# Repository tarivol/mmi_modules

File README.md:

# Modules
Original repository:
https://github.com/MMImodular/Modules

Fork of repository with MMI Modular eurorack module designs.

Designs I have changed:

1. Two Nine Five - change of components in 1.4k band, resulting in better ability to calibrate 6.5dB gain
2. Two Nine Five - added Gerber files for a basic front panel

Each directory has its own ReadMe with information on each module

If you decide to get some of your own PCBs fabbed from these files, please consider shooting the original designer! A few bucks to help support future projects!

paypal.me/AboutBlank

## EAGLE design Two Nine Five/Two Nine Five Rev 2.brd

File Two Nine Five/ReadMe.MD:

**I'm leaving the original Readme unchanged below my adaptations, to link back to the original creator - give him some love!**

## Change 1: tuning of 1.4k
TLDR; My change is extremely simple - change R34 from 15k to 18k.

### Explanation for adaptation
I noticed, that when tuning the 1.4k band I could not get the gain down to 6.5dB - the lowest position of Q trimmer achieved something akin to 6.7dB. I scratched my head for about a week searching for errors in my build, when I decided to simulate each band in LTSpice. Lo and behold - the 1.4k band with Q trimmer set to 1 Ohm and frequency pot trimmed so that the peak is at exactly 1.4k, and that gave around 6.7dB - as measured at my builds. It all stems from the fact, that the Q and freq trimmers are interacting with each other quite heavily.
Next step was preparing a tool to help finding the correct value - Copilot came to the rescue and gave me a Python script that is capable of just that. I'll leave it in the repository as well in Simulator directory. I searched for a minimal change of components, that could give me at most 6dB, preferrably 5.5dB, of gain at minimum Q position, with center frequency tuned to 1.4k. It turns out, that just bumping the R34 resistor from 15k to 18k does the trick nicely.
I replaced the resistor, calibrated the module once more and all was well :)

## Change 2: Frontpanel
I prepared a frontpanel using EasyEDA. It's similar to the one shown on the MMI Modular pictures. Gerber files can be found in Frontpanel directory.

# Original README

**If you would like to build this project yourself, PCBs can be purchased through [Pusherman](https://pushermanproductions.com/product/mmi-modular-two-nine-five-buchla-comb-filter-pcb-14hp-black-gold-aluminium-panel/) or [Modular Addict](https://modularaddict.com/mmi-259-pcbpanel)**

**If you would like to purchase a pre-built unit, keep an eye on my [Reverb shop](https://reverb.com/shop/mmi-modular)**

# Two Nine Five

* Eurorack adaptation of the Buchla Model 295 10-channel comb filter
* 10 LED sliders control the amplitude of each band sent through the SUM output
* Individual channel outputs to the right of each slider
* Tunable band frequencies, Q's, and amplitude via trim pots on the back of the module.

This recreation of the Model 295 has been in my head since before I owned any modular. After using a restored Buchla at the Oberlin Conservatory of Music, the 295 became one of my favorite modules in the whole case. Buchla modular is far out of my budget so with the original schematics in hand, I made a much more compact 3U version of it. The circuitry is exactly the same, though more modern op-amps have to be used since the ones used in the original design are no longer available.

---

**Things to note when building**

It is absolutely imperative that you solder R13, R39, R17, R37, R19, R35, R25, and R33 properly before mounting the trim pots as they will be very difficult to reach once all components are in place. To confirm they are soldered properly, measure the resistance between the two middle pins of each trim pot location. For instance, the resistance between the middle pin of VR10 and VR9 should be roughly 68 kOhms.

In addition, please heed the warning on the front of the PCB and place the trim pots on the back of the module. There is not enough space between the PCB and panel for the trim pots and having them on the back allows for you to tune everything without taking the panel off. I kept the silk screen for the pots on the top side in order to avoid cluttering the bottom silkscreen layer.

As for the illuminated slide pots, there's a few things to consider. They are acting as cross faders so any value between 10k and 100k should work just fine. They are taking an audio signal so ideally you want audio response, but linear response will function just fine. Ideal shaft length is 15mm but I have used 10mm successfully, the tops are just a tad close to the panel. You do not want a center detent if you can help it. The sliders I used can be found on Mouser: 652-PTL20-10R0-103B2

---

**How to tune your 295**

Note: You may want to keep the volume down for this or else you might give yourself a headache.

*Tuning Frequency*

* Turn each 20k trim pot so that every band has maximum gain (some bands will self-oscillate, others will not)
* Patch white noise to **IN** and monitor **SUM** with a FFT-capable spectrum analyzer or parametric/graphic EQ
* Slide the potentiometer of the band you want to tune all the way to the right
* Turn the appropriate 100k trim pot until the peak is centered on the desired frequency
* Repeat for each band

*Tuning Gain/Q*

* Using a sine wave oscillator, patch the wave directly to your output 
* Set the gain between your modular and a VU meter (usually within a DAW) so that the output is now at 0dB
* Leaving the output gain unchanged, move the sine wave to an attenuator and attenuate it down to -6.5dB
* Patch this attenuated sine wave to **IN** then patch **SUM** to your output
* Slide the potentiometer of the band you want to tune all the way to the right
* Tune your sine wave to match the frequency of the band you would like to tune
* Turn the appropriate 20k trim pot until your output is at 0dB
* Repeat for each band

It may help to monitor your output with an oscilloscope to see how your output clips. Note that each band clips asymmetrically. This can cause some interesting harmonics to show up so feel free to tune your filter to taste, no need to follow this guide to a T.

---

PCB and panel designed by me

Original schematic by Don Buchla

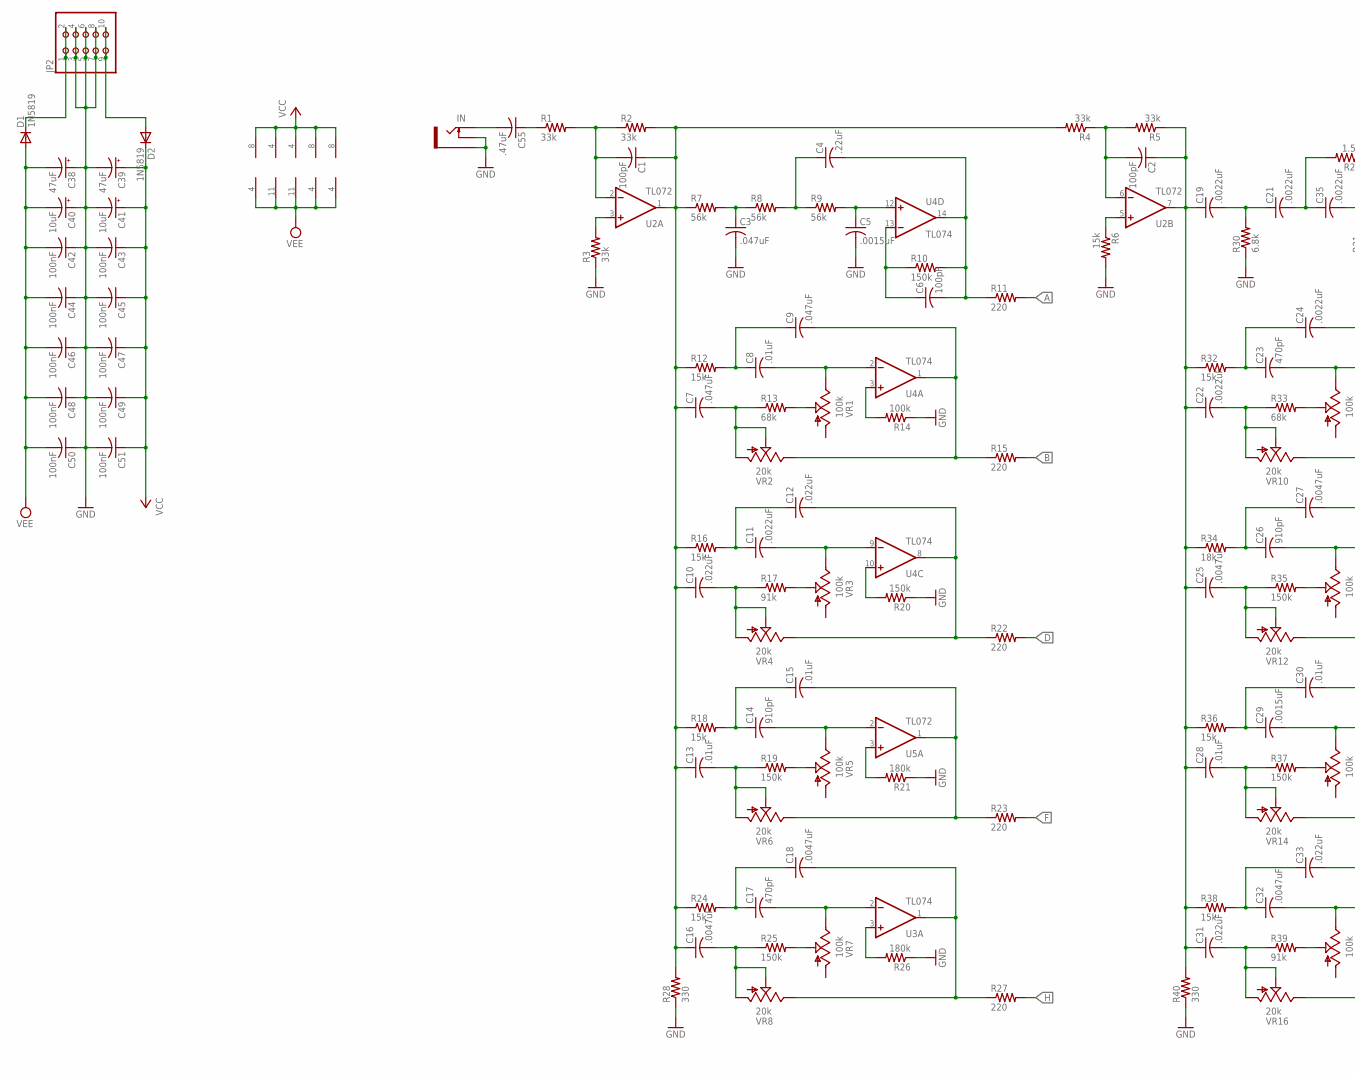
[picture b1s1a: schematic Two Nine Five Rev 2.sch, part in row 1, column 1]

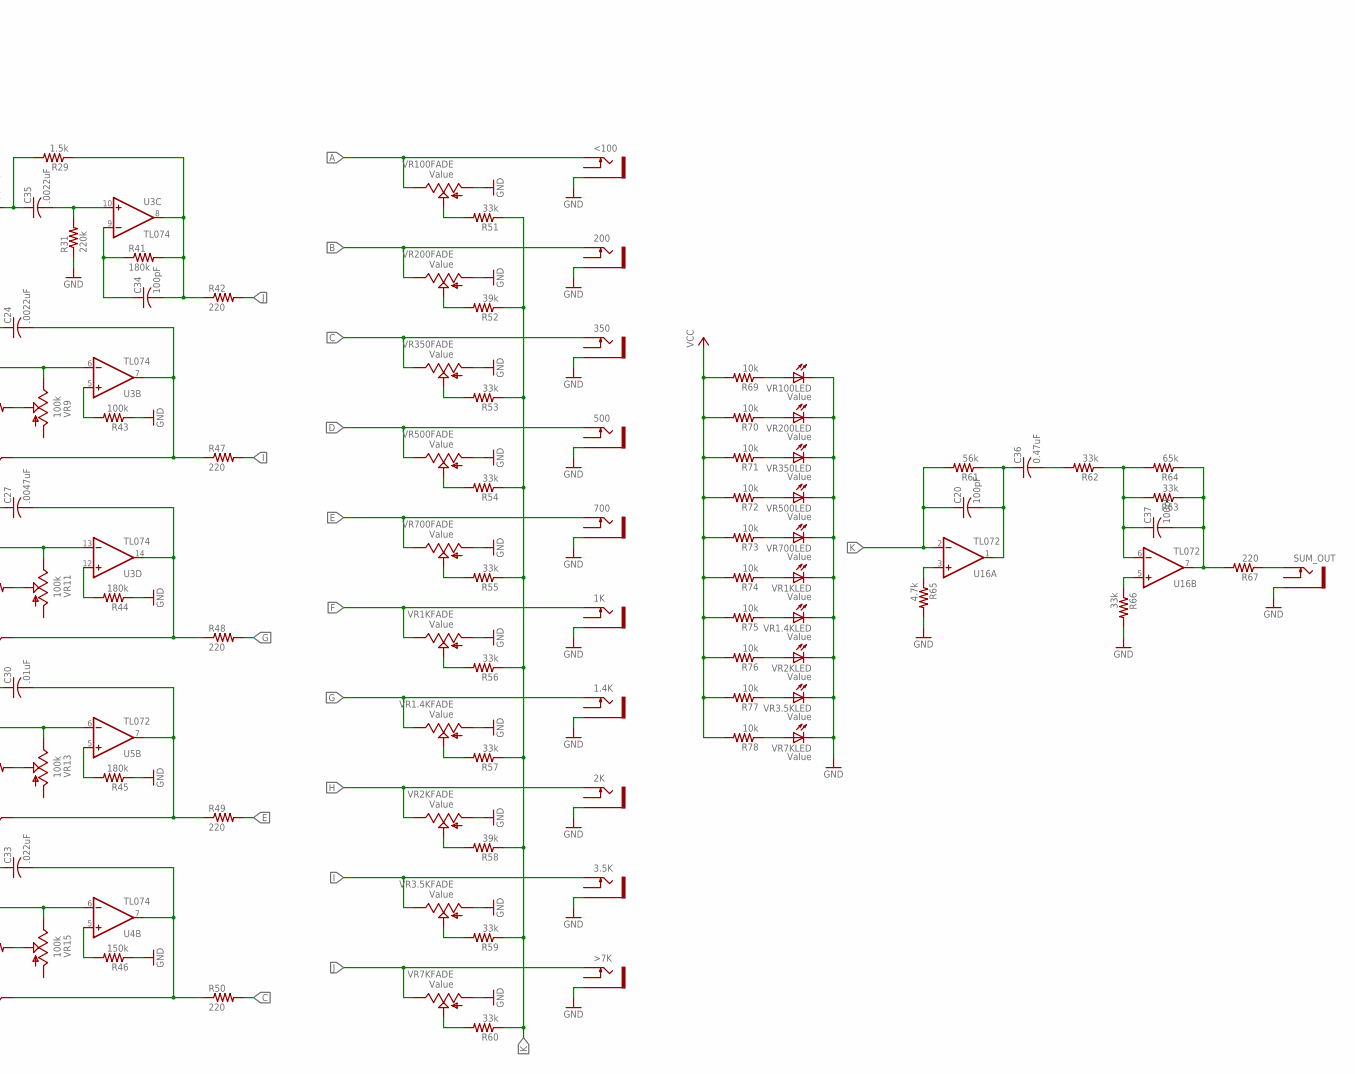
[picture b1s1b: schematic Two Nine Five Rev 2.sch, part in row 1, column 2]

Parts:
1.4K, 1K, 2K, 3.5K, 200, 350, 500, 700: THONKICONNNEW; WQP-PJ301M-12_JACK
<100: THONKICONNNEW; WQP-PJ301M-12_JACK
>7K: THONKICONNNEW; WQP-PJ301M-12_JACK
C1, C2, C6, C20, C34, C37: 100pF; C0603
C3, C7, C9: .047uF; C0603
C4: .22uF; C0603
C5, C29: .0015uF; C0603
C8, C13, C15, C28, C30: .01uF; C0603
C10, C12, C31, C33: .022uF; C0603
C11, C19, C21, C22, C24, C35: .0022uF; C0603
C14, C26: 910pF; C0603
C16, C18, C25, C27, C32: .0047uF; C0603
C17, C23: 470pF; C0603
C36: 0.47uF; C0603
C38, C39: 47uF; PANASONIC_D
C40, C41: 10uF; PANASONIC_B
C42, C43, C44, C45, C46, C47, C48, C49, C50, C51: 100nF; C0603
C55: .47uF; C0603
D1, D2: 1N5819; SOD123
IN: THONKICONNNEW; WQP-PJ301M-12_JACK
JP2: PINHD-2X5SMT; 2X05_SMT
R1, R2, R3, R4, R5, R51, R53, R54, R55, R56, R57, R59, R60, R62, R63, R66: 33k; R0603
R6, R12, R16, R18, R24, R32, R36, R38: 15k; R0603
R7, R8, R9, R61: 56k; R0603
R10, R19, R20, R25, R35, R37, R46: 150k; R0603
R11, R15, R22, R23, R27, R42, R47, R48, R49, R50, R67: 220; R0603
R13, R33: 68k; R0603
R14, R43: 100k; R0603
R17, R39: 91k; R0603
R21, R26, R41, R44, R45: 180k; R0603
R28, R40: 330; R0603
R29: 1.5k; R0603
R30: 6.8k; R0603
R31: 220k; R0603
R34: 18k; R0603
R52, R58: 39k; R0603
R64: 65k; R0603
R65: 4.7k; R0603
R69, R70, R71, R72, R73, R74, R75, R76, R77, R78: 10k; R0603
SUM_OUT: THONKICONNNEW; WQP-PJ301M-12_JACK
U2, U5, U16: TL072; SO08
U3, U4: TL074; SO14
VR1, VR3, VR5, VR7, VR9, VR11, VR13, VR15: 100k; RJ9W
VR1.4K, VR1K, VR2K, VR3.5K, VR7K, VR100, VR200, VR350, VR500, VR700: Value; ALPHA_ILL_FADER_20MM_REV2
VR2, VR4, VR6, VR8, VR10, VR12, VR14, VR16: 20k; RJ9W

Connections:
A: <100.P$1_TIP (TIP), R11.2, VR100.1 (E)
B: 200.P$1_TIP (TIP), R15.2, VR200.1 (E)
C: 350.P$1_TIP (TIP), R50.2, VR350.1 (E)
D: 500.P$1_TIP (TIP), R22.2, VR500.1 (E)
E: 700.P$1_TIP (TIP), R49.2, VR700.1 (E)
F: 1K.P$1_TIP (TIP), R23.2, VR1K.1 (E)
G: 1.4K.P$1_TIP (TIP), R48.2, VR1.4K.1 (E)
GND: 1.4K.P$3_SLEEVE (SLEEVE), 1K.P$3_SLEEVE (SLEEVE), 2K.P$3_SLEEVE (SLEEVE), 3.5K.P$3_SLEEVE (SLEEVE), 200.P$3_SLEEVE (SLEEVE), 350.P$3_SLEEVE (SLEEVE), 500.P$3_SLEEVE (SLEEVE), 700.P$3_SLEEVE (SLEEVE), <100.P$3_SLEEVE (SLEEVE), >7K.P$3_SLEEVE (SLEEVE), C3.2, C5.2, C38.+, C39.-, C40.+, C41.-, C42.1, C43.2, C44.1, C45.2, C46.1, C47.2, C48.1, C49.2, C50.1, C51.2, IN.P$2_SWITCH (SWITCH), IN.P$3_SLEEVE (SLEEVE), JP2.3, JP2.4, JP2.5, JP2.6, JP2.7, JP2.8, R3.1, R6.2, R14.1, R20.1, R21.1, R26.1, R28.1, R30.1, R31.1, R40.1, R43.1, R44.1, R45.1, R46.1, R65.2, R66.2, SUM_OUT.P$3_SLEEVE (SLEEVE), VR1.4K.3 (A), VR1.4K.E (C), VR1K.3 (A), VR1K.E (C), VR2K.3 (A), VR2K.E (C), VR3.5K.3 (A), VR3.5K.E (C), VR7K.3 (A), VR7K.E (C), VR100.3 (A), VR100.E (C), VR200.3 (A), VR200.E (C), VR350.3 (A), VR350.E (C), VR500.3 (A), VR500.E (C), VR700.3 (A), VR700.E (C)
H: 2K.P$1_TIP (TIP), R27.2, VR2K.1 (E)
I: 3.5K.P$1_TIP (TIP), R47.2, VR3.5K.1 (E)
J: >7K.P$1_TIP (TIP), R42.2, VR7K.1 (E)
K: C20.1, R51.1, R52.1, R53.1, R54.1, R55.1, R56.1, R57.1, R58.1, R59.1, R60.1, R61.2, U16.2 (-IN)
unnamed: C55.2, IN.P$1_TIP (TIP)
unnamed: C1.2, R1.2, R2.1, U2.2 (-IN)
unnamed: C1.1, C7.1, C10.1, C13.1, C16.1, R2.2, R4.2, R7.1, R12.1, R16.1, R18.1, R24.1, R28.2, U2.1 (OUT)
unnamed: R3.2, U2.3 (+IN)
unnamed: C3.1, R7.2, R8.1
unnamed: C2.2, R4.1, R5.2, U2.6 (-IN)
unnamed: C2.1, C19.1, C22.1, C25.1, C28.1, C31.1, R5.1, R32.1, R34.1, R36.1, R38.1, R40.2, U2.7 (OUT)
unnamed: R6.1, U2.5 (+IN)
unnamed: C4.1, R8.2, R9.1
unnamed: C5.1, R9.2, U4.12 (+IN)
unnamed: C4.2, C6.2, R10.2, R11.1, U4.14 (OUT)
unnamed: C6.1, R10.1, U4.13 (-IN)
unnamed: C8.1, C9.1, R12.2
unnamed: C7.2, R13.1, VR2.A, VR2.S
unnamed: R13.2, VR1.S
unnamed: C8.2, U4.2 (-IN), VR1.E
unnamed: R14.2, U4.3 (+IN)
unnamed: C9.2, R15.1, U4.1 (OUT), VR2.E
unnamed: R26.2, U3.3 (+IN)
unnamed: C11.1, C12.1, R16.2
unnamed: C10.2, R17.1, VR4.A, VR4.S
unnamed: R17.2, VR3.S
unnamed: C11.2, U4.9 (-IN), VR3.E
unnamed: C12.2, R22.1, U4.8 (OUT), VR4.E
unnamed: C17.1, C18.1, R24.2
unnamed: C14.1, C15.1, R18.2
unnamed: C13.2, R19.1, VR6.A, VR6.S
unnamed: R19.2, VR5.S
unnamed: C14.2, U5.2 (-IN), VR5.E
unnamed: C15.2, R23.1, U5.1 (OUT), VR6.E
unnamed: R20.2, U4.10 (+IN)
unnamed: R21.2, U5.3 (+IN)
unnamed: C16.2, R25.1, VR8.A, VR8.S
unnamed: R25.2, VR7.S
unnamed: C17.2, U3.2 (-IN), VR7.E
unnamed: C18.2, R27.1, U3.1 (OUT), VR8.E
unnamed: C19.2, C21.1, R30.2
unnamed: C35.2, R31.2, U3.10 (+IN)
unnamed: C21.2, C35.1, R29.2
unnamed: R65.1, U16.3 (+IN)
unnamed: C34.2, R29.1, R41.2, R42.1, U3.8 (OUT)
unnamed: C23.1, C24.1, R32.2
unnamed: C22.2, R33.1, VR10.A, VR10.S
unnamed: R39.2, VR15.S
unnamed: C23.2, U3.6 (-IN), VR9.E
unnamed: C24.2, R47.1, U3.7 (OUT), VR10.E
unnamed: C26.1, C27.1, R34.2
unnamed: C25.2, R35.1, VR12.A, VR12.S
unnamed: R37.2, VR13.S
unnamed: C26.2, U3.13 (-IN), VR11.E
unnamed: C27.2, R48.1, U3.14 (OUT), VR12.E
unnamed: C29.1, C30.1, R36.2
unnamed: C28.2, R37.1, VR14.A, VR14.S
unnamed: R35.2, VR11.S
unnamed: C29.2, U5.6 (-IN), VR13.E
unnamed: C30.2, R49.1, U5.7 (OUT), VR14.E
unnamed: C32.1, C33.1, R38.2
unnamed: C31.2, R39.1, VR16.A, VR16.S
unnamed: R33.2, VR9.S
unnamed: C32.2, U4.6 (-IN), VR15.E
unnamed: C33.2, R50.1, U4.7 (OUT), VR16.E
unnamed: R51.2, VR100.2 (S)
unnamed: C34.1, R41.1, U3.9 (-IN)
unnamed: R43.2, U3.5 (+IN)
unnamed: R44.2, U3.12 (+IN)
unnamed: R45.2, U5.5 (+IN)
unnamed: R46.2, U4.5 (+IN)
unnamed: R66.1, U16.5 (+IN)
unnamed: R52.2, VR200.2 (S)
unnamed: C20.2, C36.1, R61.1, U16.1 (OUT)
unnamed: R53.2, VR350.2 (S)
unnamed: C36.2, R62.2
unnamed: R54.2, VR500.2 (S)
unnamed: C37.1, R62.1, R63.2, R64.2, U16.6 (-IN)
unnamed: R55.2, VR700.2 (S)
unnamed: C37.2, R63.1, R64.1, R67.2, U16.7 (OUT)
unnamed: R56.2, VR1K.2 (S)
unnamed: R67.1, SUM_OUT.P$1_TIP (TIP)
unnamed: R57.2, VR1.4K.2 (S)
unnamed: D2.A, JP2.9, JP2.10
unnamed: R58.2, VR2K.2 (S)
unnamed: R69.1, VR100.B (A)
unnamed: R59.2, VR3.5K.2 (S)
unnamed: D1.C, JP2.1, JP2.2
unnamed: R60.2, VR7K.2 (S)
unnamed: R70.1, VR200.B (A)
unnamed: R71.1, VR350.B (A)
unnamed: R72.1, VR500.B (A)
unnamed: R73.1, VR700.B (A)
unnamed: R74.1, VR1K.B (A)
unnamed: R75.1, VR1.4K.B (A)
unnamed: R76.1, VR2K.B (A)
unnamed: R77.1, VR3.5K.B (A)
unnamed: R78.1, VR7K.B (A)
unnamed: C55.1, R1.1
VCC: C39.+, C41.+, C43.1, C45.1, C47.1, C49.1, C51.1, D2.C, R69.2, R70.2, R71.2, R72.2, R73.2, R74.2, R75.2, R76.2, R77.2, R78.2, U2.8 (V+), U3.4 (V+), U4.4 (V+), U5.8 (V+), U16.8 (V+)
VEE: C38.-, C40.-, C42.2, C44.2, C46.2, C48.2, C50.2, D1.A, U2.4 (V-), U3.11 (V-), U4.11 (V-), U5.4 (V-), U16.4 (V-)

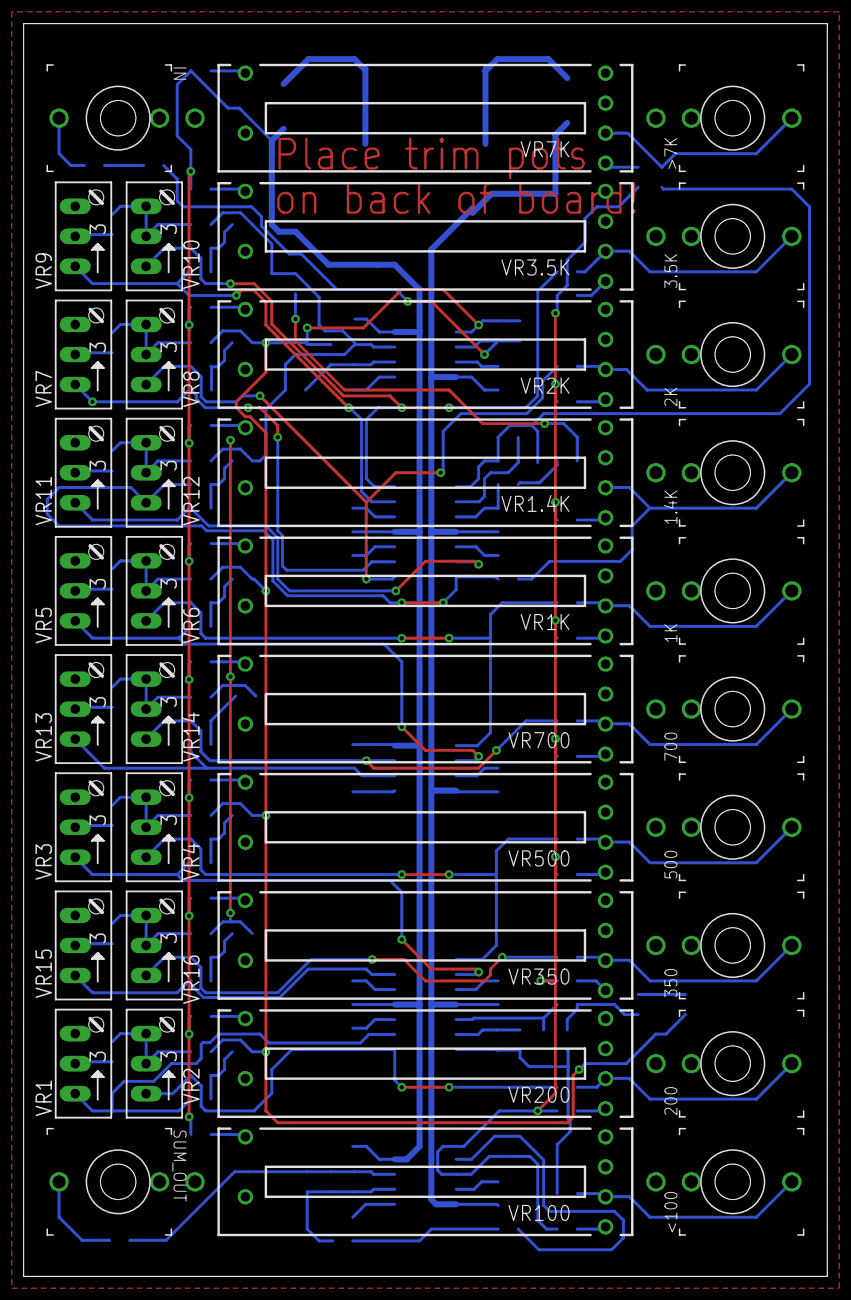
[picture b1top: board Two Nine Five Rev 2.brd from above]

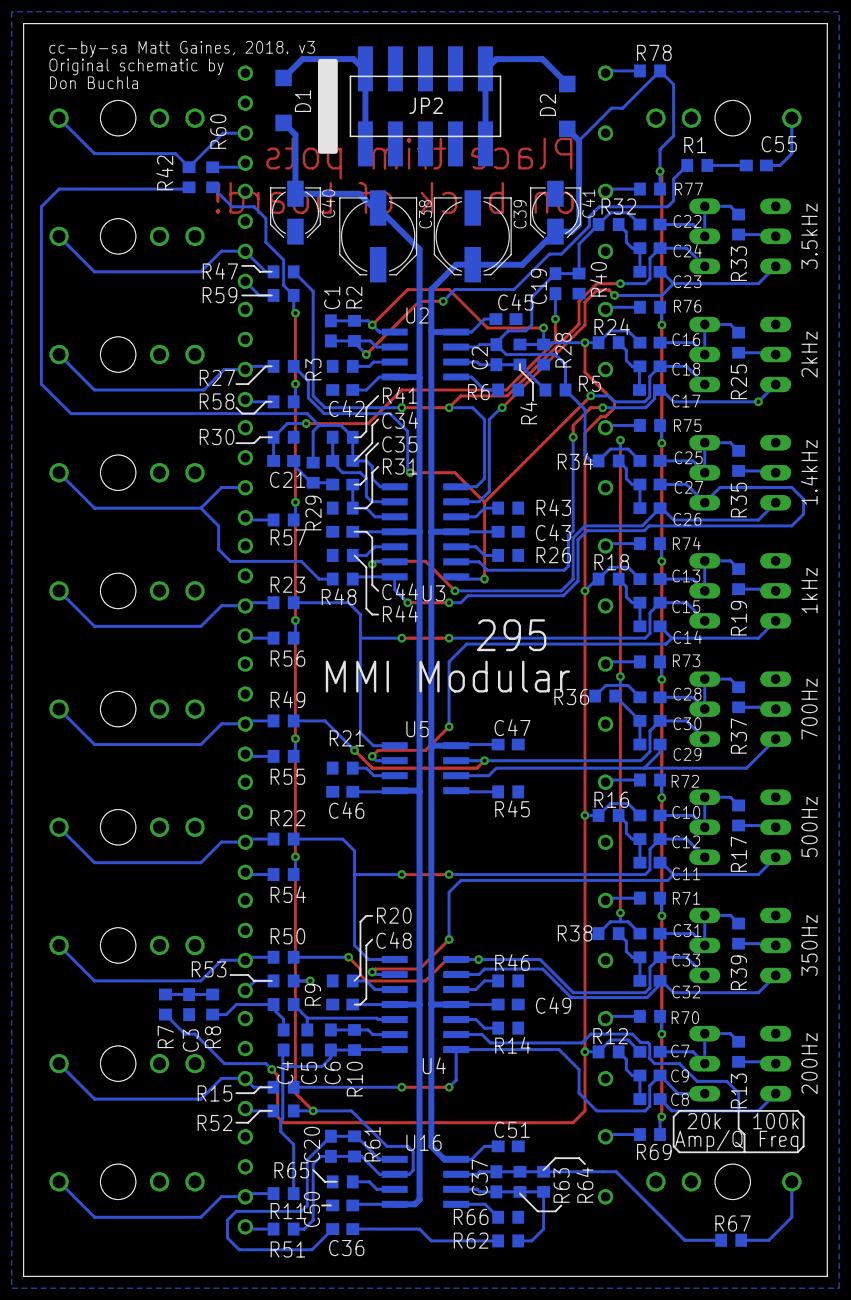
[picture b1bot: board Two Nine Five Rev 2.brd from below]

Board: 2 copper layers, 68.0 x 106.0 mm, 175 parts (137 on the bottom side), 109 nets.

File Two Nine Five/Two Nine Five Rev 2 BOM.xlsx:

Qty | Value | Device | Package | Parts | Description | SPICEPREFIX | Column1
1 |  | PINHD-2X5SMT | 2X05_SMT | JP2 | PIN HEADER
2 | .0015uF | C-USC0603 | C0603 | C5, C29 | CAPACITOR, American symbol
6 | .0022uF | C-USC0603 | C0603 | C11, C19, C21, C22, C24, C35 | CAPACITOR, American symbol
5 | .0047uF | C-USC0603 | C0603 | C16, C18, C25, C27, C32 | CAPACITOR, American symbol
5 | .01uF | C-USC0603 | C0603 | C8, C13, C15, C28, C30 | CAPACITOR, American symbol
4 | .022uF | C-USC0603 | C0603 | C10, C12, C31, C33 | CAPACITOR, American symbol
3 | .047uF | C-USC0603 | C0603 | C3, C7, C9 | CAPACITOR, American symbol
1 | .22uF | C-USC0603 | C0603 | C4 | CAPACITOR, American symbol
2 | .47uF | C-USC0603 | C0603 | C36, C55 | CAPACITOR, American symbol
1 | 1.5k | R-US_R0603 | R0603 | R29 | RESISTOR, American symbol
2 | 100k | R-US_R0603 | R0603 | R14, R43 | RESISTOR, American symbol
8 | 100k | TRIM_US-RJ9W | RJ9W | VR1, VR3, VR5, VR7, VR9, VR11, VR13, VR15 | POTENTIOMETER
10 | 100nF | C-USC0603 | C0603 | C42, C43, C44, C45, C46, C47, C48, C49, C50, C51 | CAPACITOR, American symbol
6 | 100pF | C-USC0603 | C0603 | C1, C2, C6, C20, C34, C37 | CAPACITOR, American symbol
10 | 10k | R-US_R0603 | R0603 | R69, R70, R71, R72, R73, R74, R75, R76, R77, R78 | RESISTOR, American symbol
2 | 10uF | CPOL-USB | PANASONIC_B | C40, C41 | POLARIZED CAPACITOR, American symbol | C
7 | 150k | R-US_R0603 | R0603 | R10, R19, R20, R25, R35, R37, R46 | RESISTOR, American symbol
8 | 15k | R-US_R0603 | R0603 | R6, R12, R16, R18, R24, R32, R36, R38 | RESISTOR, American symbol
1 | 18k | R-US_R0603 | R0603 | R34 | RESISTOR, American symbol
5 | 180k | R-US_R0603 | R0603 | R21, R26, R41, R44, R45 | RESISTOR, American symbol
2 | 1N5819 | DIODE-SOD123 | SOD123 | D1, D2 | DIODE
8 | 20k | TRIM_US-RJ9W | RJ9W | VR2, VR4, VR6, VR8, VR10, VR12, VR14, VR16 | POTENTIOMETER
11 | 220 | R-US_R0603 | R0603 | R11, R15, R22, R23, R27, R42, R47, R48, R49, R50, R67 | RESISTOR, American symbol
1 | 220k | R-US_R0603 | R0603 | R31 | RESISTOR, American symbol
2 | 330 | R-US_R0603 | R0603 | R28, R40 | RESISTOR, American symbol
16 | 33k | R-US_R0603 | R0603 | R1, R2, R3, R4, R5, R51, R53, R54, R55, R56, R57, R59, R60, R62, R63, R66 | RESISTOR, American symbol
2 | 39k | R-US_R0603 | R0603 | R52, R58 | RESISTOR, American symbol
1 | 4.7k | R-US_R0603 | R0603 | R65 | RESISTOR, American symbol
2 | 470pF | C-USC0603 | C0603 | C17, C23 | CAPACITOR, American symbol
2 | 47uF | CPOL-USD | PANASONIC_D | C38, C39 | POLARIZED CAPACITOR, American symbol | C
4 | 56k | R-US_R0603 | R0603 | R7, R8, R9, R61 | RESISTOR, American symbol
1 | 6.8k | R-US_R0603 | R0603 | R30 | RESISTOR, American symbol
1 | 65k | R-US_R0603 | R0603 | R64 | RESISTOR, American symbol
2 | 68k | R-US_R0603 | R0603 | R13, R33 | RESISTOR, American symbol
2 | 910pF | C-USC0603 | C0603 | C14, C26 | CAPACITOR, American symbol
2 | 91k | R-US_R0603 | R0603 | R17, R39 | RESISTOR, American symbol
12 | THONKICONNNEW | THONKICONNNEW | WQP-PJ301M-12_JACK | 1.4K, 1K, 2K, 3.5K, 200, 350, 500, 700, <100, >7K, IN, SUM_OUT | 3.5mm socket for Eurorack modular synths
3 | TL072 | TL072_SMD | SO08 | U2, U5, U16 | Generic Dual Op Amp
2 | TL074 | TL074_SMD | SO14 | U3, U4 | Generic Quad Op Amp
10 | Value | ALPHA_20MM_ILLUM_FADER | ALPHA_ILL_FADER_20MM_REV2 | VR1.4K, VR1K, VR2K, VR3.5K, VR7K, VR100, VR200, VR350, VR500, VR700 | 20mm Alpha Illuminated Fader

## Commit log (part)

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2026-06-19 Revise README with original repository and designer support
    Updated README to include original repository link and clarify support for original designer.
2026-06-19 Update ReadMe with tuning adaptations and frontpanel info
    Added detailed explanations for tuning changes and frontpanel design.
2026-06-19 Revise ReadMe for tuning adjustments and resistor change
    Updated the ReadMe file to include detailed explanation of tuning changes and resistor modifications for the 1.4k band.
2026-06-19 Text cleanup

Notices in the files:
Two Nine Five/Two Nine Five Rev 2.brd:
cc-by-sa Matt Gaines, 2018. v3
